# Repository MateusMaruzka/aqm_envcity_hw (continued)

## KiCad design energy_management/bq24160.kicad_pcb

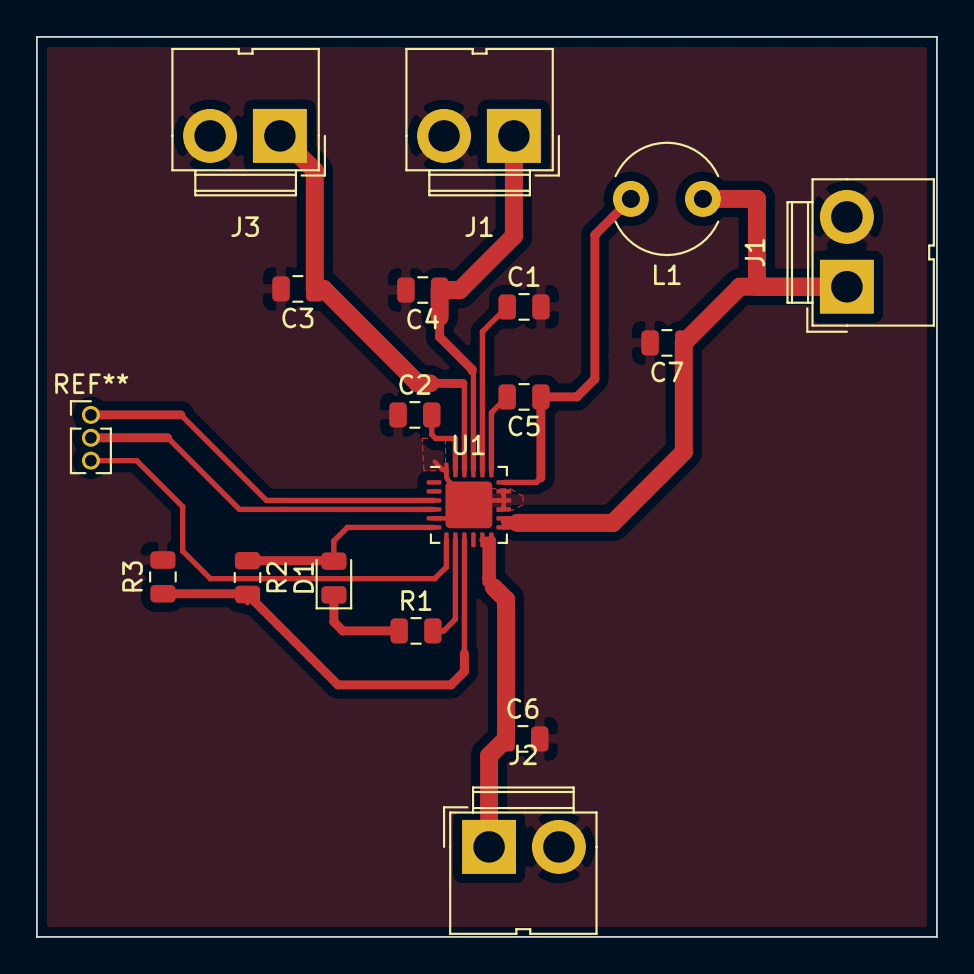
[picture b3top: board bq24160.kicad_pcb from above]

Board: 2 copper layers, 50.0 x 50.0 mm, 17 parts (0 on the bottom side), 13 nets.

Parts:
C1, C2: 4,7uF; C_0805_2012Metric
C3, C4, C6, C7: 1uF; C_0805_2012Metric
C5: 0,01uF; C_0805_2012Metric
D1: LED; LED_0805_2012Metric
J1, J1#2, J2: Conn_01x02_Male; JWT_A3963_1x02_P3.96mm_Vertical
J3: Conn_01x02_Female; JWT_A3963_1x02_P3.96mm_Vertical
L1: 1,5uH; L_Radial_D6.0mm_P4.00mm
R1: 1K; R_0805_2012Metric
R2: 10k; R_0805_2012Metric
R3: 10K; R_0805_2012Metric
U1: BQ24160RGET; QFN-24-1EP_4x4mm_P0.5mm_EP2.6x2.6mm

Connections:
/BAT_NTC: R2.2, R3.1, U1.9
/BOOT: C5.2, U1.19
/PMIDU: C2.2, U1.23
/STAT: R1.2, U1.8
/SW: C5.1, L1.2, U1.18
/VBAT: C6.1, J2.1, U1.11, U1.12
/VDRV: D1.2, R2.1, U1.6
/Vext_dc: C4.1, J1#2.1, U1.21
/Vsistema: C7.1, J1.1, L1.1, U1.13, U1.14
/Vusb: C3.1, J3.1, U1.22
GND: C1.2, C2.1, C3.2, C4.2, C6.2, C7.2, J1.2, J1#2.2, J2.2, J3.2, R3.2, U1.5, U1.15, U1.16, U1.17, U1.24, U1.25
unnamed: C1.1, U1.20
unnamed: D1.1, R1.1

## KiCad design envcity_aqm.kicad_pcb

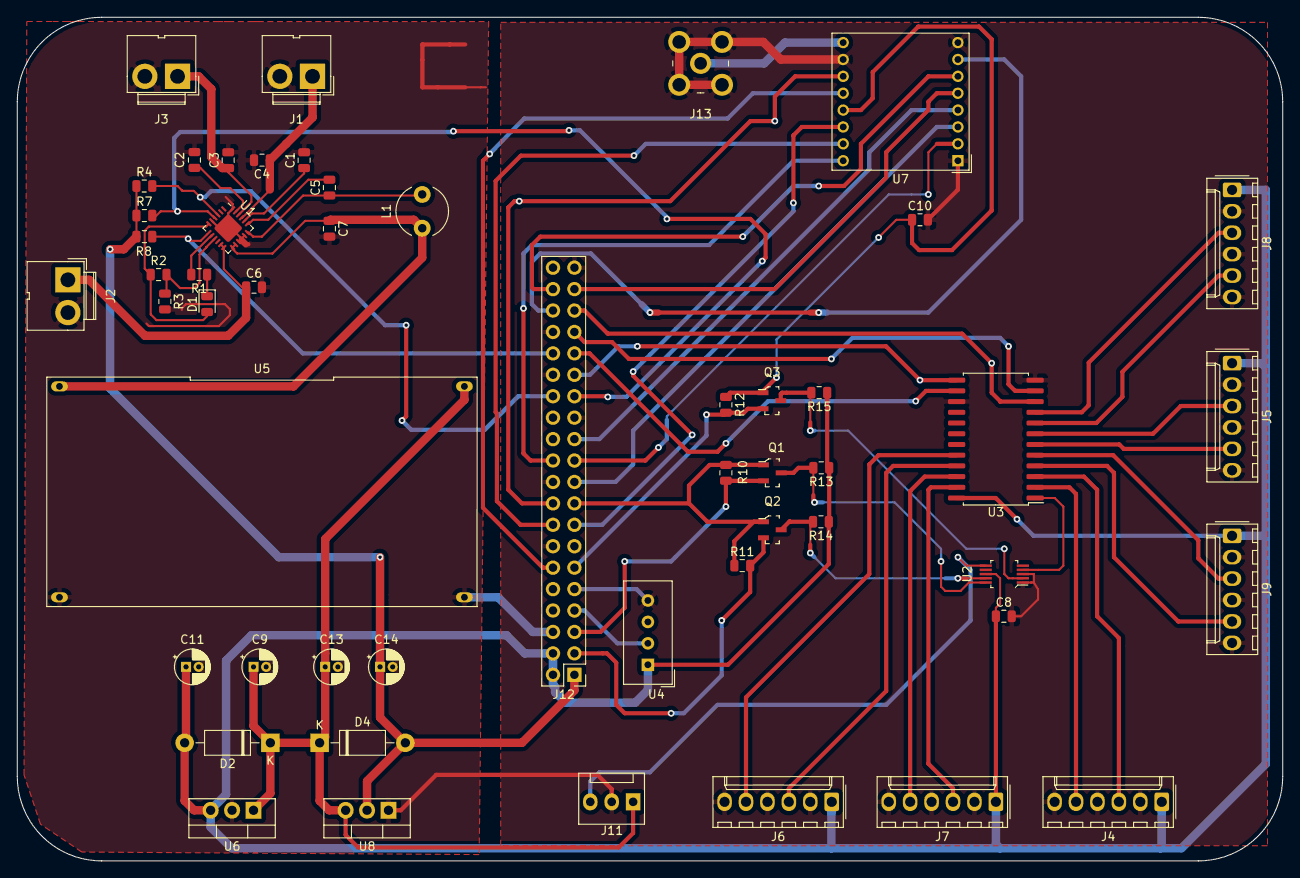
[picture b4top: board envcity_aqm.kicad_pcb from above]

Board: 2 copper layers, 150.0 x 100.0 mm, 52 parts (0 on the bottom side), 56 nets.

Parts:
C1, C2: 4,7uF; C_0805_2012Metric
C3, C4, C6, C7, C8: 1uF; C_0805_2012Metric
C5: 0,01uF; C_0805_2012Metric
C9, C13: 0,33uF; CP_Radial_D4.0mm_P1.50mm
C10: 100nF; C_0805_2012Metric
C11, C14: 0,1uF; CP_Radial_D4.0mm_P1.50mm
D1: LED; LED_0805_2012Metric
D2, D4: 1N4001; D_DO-41_SOD81_P10.16mm_Horizontal
J1, J2: Conn_01x02_Male; JWT_A3963_1x02_P3.96mm_Vertical
J3: Conn_01x02_Female; JWT_A3963_1x02_P3.96mm_Vertical
J4, J5, J6, J7, J8, J9: Conn_01x06_Male; Molex_KK-254_AE-6410-06A_1x06_P2.54mm_Vertical
J11: Conn_01x03_Female; FanPinHeader_1x03_P2.54mm_Vertical
J12: Conn_02x20_Odd_Even; PinHeader_2x20_P2.54mm_Vertical
J13: 5-1814400-1; RF_SMA_RightAngle_5-1814400-1
L1: 1,5uH; L_Radial_D6.0mm_P4.00mm
Q1, Q2, Q3: BSS138; SOT-23-3
R1: 1K; R_0805_2012Metric
R2, R4, R7, R8, R10, R11, R12, R13, R14, R15: 10k; R_0805_2012Metric
R3: 10K; R_0805_2012Metric
U1: BQ24160RGET; VQFN-24-1EP_4x4mm_P0.5mm_EP2.45x2.45mm
U2: ADS1115IDGST; MSOP-10_W3mm
U3: CD74HC4067M; SOIC-24W_7.5x15.4mm_P1.27mm
U4: DHT11; Aosong_DHT11_5.5x12.0_P2.54mm
U5: BUCK_BOOST_BOARD; DIP-4_1889_ELL
U6: LM7805_TO220; TO-220-3_Vertical
U7: RFM95W-915S2; HOPERF_RFM9XW_THT
U8: LM1117-3.3; TO-220-3_Vertical

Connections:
+3V3: C10.1, C14.1, D4.2, J12.1, J12.17, Q1.1, Q2.1, Q3.1, R4.1, R7.1, R8.1, R10.1, R11.1, R12.1, U7.13, U8.2
+5V: C8.1, C11.1, D2.2, J4.1, J5.1, J6.1, J7.1, J8.1, J9.1, J12.2, J12.4, R13.1, R14.1, R15.1, U2.8, U3.24, U4.1, U6.3
/9Vin: C9.1, C13.1, D2.1, D4.1, J11.1, U5.3, U6.1, U8.3
/ADS1115+MUX/AIN0: U2.4, U3.1
/AD_ALERT: Q3.3, R15.2, U2.2
/AD_SCL: Q1.3, R13.2, U2.10
/AD_SDA: Q2.3, R14.2, U2.9
/BQ_INT: J12.32, R8.2, U1.7
/BQ_SCL: J12.28, R4.2, U1.3
/BQ_SDA: J12.27, R7.2, U1.4
/DHT22: J12.7, U4.2
/DIO0: J12.15, U7.14
/DIO1: J12.16, U7.15
/DIO2: J12.22, U7.16
/DIO3: J12.18, U7.11
/DIO4: J12.12, U7.12
/DIO5: J12.36, U7.7
/Gerenciamento de Bateria/BAT_NTC: R2.2, R3.1, U1.9
/Gerenciamento de Bateria/BOOT: C5.2, U1.19
/Gerenciamento de Bateria/PMIDU: C2.2, U1.23
/Gerenciamento de Bateria/STAT: R1.2, U1.8
/Gerenciamento de Bateria/SW: C5.1, L1.2, U1.18
/Gerenciamento de Bateria/VBAT: C6.1, J2.1, U1.11, U1.12
/Gerenciamento de Bateria/VDRV: D1.2, R2.1, U1.6
/Gerenciamento de Bateria/Vext_dc: C4.1, J1.1, U1.21
/Gerenciamento de Bateria/Vusb: C3.1, J3.1, U1.22
/I0: J8.3, U3.9
/I1: J8.5, U3.8
/I2: J5.3, U3.7
/I3: J5.5, U3.6
/I4: J9.3, U3.5
/I5: J9.5, U3.4
/I6: J4.3, U3.3
/I7: J4.5, U3.2
/I8: J7.3, U3.23
/I9: J7.5, U3.22
/I10: J6.3, U3.21
/I11: J6.5, U3.20
/NSS: J12.37, U7.5
/RASP_INT0: J12.11, Q3.2, R12.2
/RASP_SCL0: J12.5, Q1.2, R10.2
/RASP_SDA0: J12.3, Q2.2, R11.2
/RESET: J12.38, U7.6
/Radio LoRa RFM95W/ANT: J13.2, U7.9
/Reguladores/Vin: C7.1, L1.1, U1.13, U1.14, U5.1
/S0: J12.35, U3.10
/S1: J12.33, U3.11
/S2: J12.31, U3.14
/S3: J12.29, U3.13
/SPI0_0: J12.19, U7.3
/SPI0_1: J12.21, U7.2
/SPI0_2: J12.23, U7.4
AIN2: J11.3, U2.6
GND: C1.2, C2.1, C3.2, C4.2, C6.2, C7.2, C8.2, C9.2, C10.2, C11.2, C13.2, C14.2, J1.2, J2.2, J3.2, J4.2, J4.4, J4.6, J5.2, J5.4, J5.6, J6.2, J6.4, J6.6, J7.2, J7.4, J7.6, J8.2, J8.4, J8.6, J9.2, J9.4, J9.6, J11.2, J12.6, J12.9, J12.14, J12.20, J12.25, J12.30, J12.34, J12.39, J13.1, R3.2, U1.5, U1.15, U1.16, U1.17, U1.24, U1.25, U2.1, U2.3, U3.12, U3.15, U4.4, U5.2, U5.4, U6.2, U7.1, U7.8, U7.10, U8.1
unnamed: C1.1, U1.20
unnamed: D1.1, R1.1

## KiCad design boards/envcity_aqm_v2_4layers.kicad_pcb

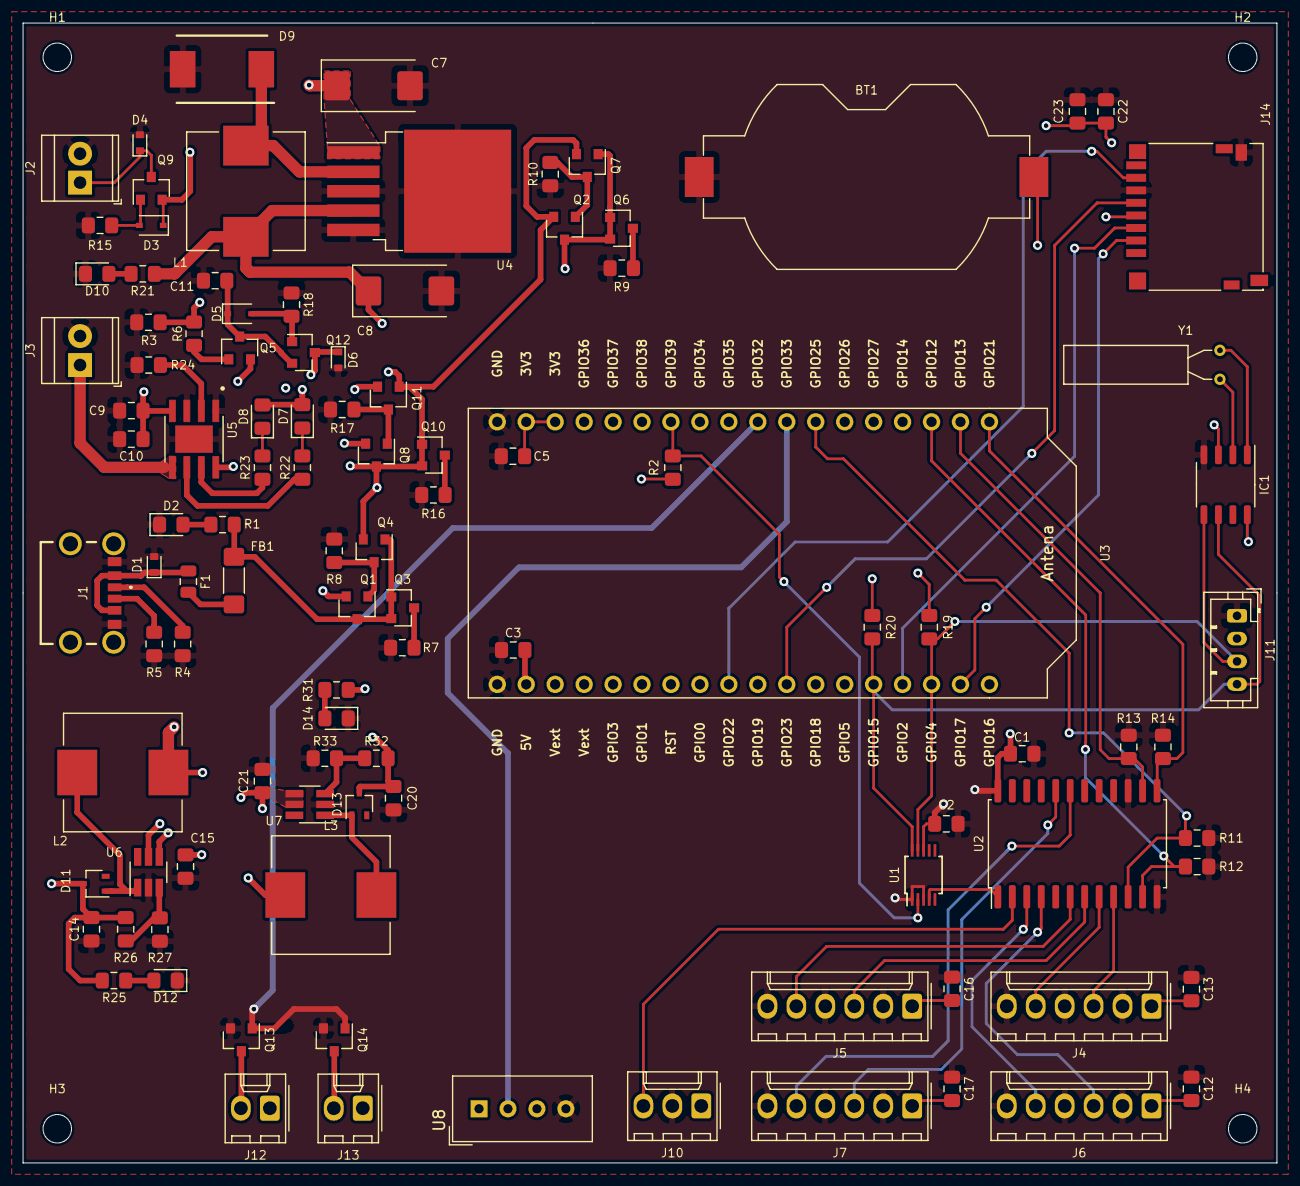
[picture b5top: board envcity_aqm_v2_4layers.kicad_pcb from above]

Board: 4 copper layers, 110.0 x 100.0 mm, 109 parts (0 on the bottom side), 67 nets.

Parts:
BT1: Battery_Cell; BatteryHolder_Keystone_1058_1x2032
C1, C9, C11, C22: 10uF; C_0805_2012Metric_Pad1.15x1.40mm_HandSolder
C2, C3, C5, C10, C12, C13, C16, C17, C23: 100nF; C_0805_2012Metric_Pad1.15x1.40mm_HandSolder
C7: 680uF - Tant; CP_EIA-7343-15_Kemet-W_Pad2.25x2.55mm_HandSolder
C8: 220uF-Tantalum; CP_EIA-7343-15_Kemet-W_Pad2.25x2.55mm_HandSolder
C14, C15, C20, C21: 22uF-X5R; C_0805_2012Metric_Pad1.15x1.40mm_HandSolder
D1, D4, D6: D_TVS_ALT; D_SOD-523
D2, D7, D8, D10, D12, D14: LED; LED_0805_2012Metric_Pad1.15x1.40mm_HandSolder
D3, D5: 5V; D_SOD-323
D9: SS34; DIOM8059X256N
D11, D13: BAT54W; SOT-323_SC-70
F1: Fuse; Fuse_0805_2012Metric
FB1: Ferrite_Bead; L_1806_4516Metric_Pad1.57x1.80mm_HandSolder
H1, H2, H3, H4: MountingHole; MountingHole_2.5mm
IC1: DS1307ZN+; SOP-8_3.9x4.9mm_P1.27mm
J1: 217175-0001; 2171750001
J2, J3: Screw_Terminal_01x02; TerminalBlock_TE_282834-2_1x02_P2.54mm_Horizontal
J4, J5, J6, J7: Conn_01x06_Male; Molex_KK-254_AE-6410-06A_1x06_P2.54mm_Vertical
J10: Conn_01x03_Male; Molex_KK-254_AE-6410-03A_1x03_P2.54mm_Vertical
J11: Conn_01x04_Male; JST_PH_B4B-PH-K_1x04_P2.00mm_Vertical
J12, J13: Conn_01x02_Male; Molex_KK-254_AE-6410-02A_1x02_P2.54mm_Vertical
J14: Micro_SD_Card; microSD_HC_Hirose_DM3D-SF
L1: 33uH; L_Wuerth_HCI-1040
L2, L3: 4.7 to 22uH; L_Wuerth_HCI-1040
Q1, Q2, Q8: DMG2301L; SOT-23
Q3, Q4, Q6, Q7, Q10, Q11: BC808; SOT-23
Q5, Q9, Q12: DMG2301L / DMP2045U; SOT-23
Q13, Q14: DMN10H220L; SOT-23
R1, R2, R11, R12, R13, R14, R19, R20, R21, R22, R23, R31: 4K7; R_0805_2012Metric_Pad1.15x1.40mm_HandSolder
R3, R6, R7, R9, R16: 10K; R_0805_2012Metric_Pad1.15x1.40mm_HandSolder
R4, R5: 5K1; R_0805_2012Metric_Pad1.15x1.40mm_HandSolder
R8, R10, R17: 47K; R_0805_2012Metric_Pad1.15x1.40mm_HandSolder
R15, R18, R33: 1K; R_0805_2012Metric_Pad1.15x1.40mm_HandSolder
R24: 2K; R_0805_2012Metric_Pad1.15x1.40mm_HandSolder
R25: 9K1; R_0805_2012Metric_Pad1.15x1.40mm_HandSolder
R26: 30K; R_0805_2012Metric_Pad1.15x1.40mm_HandSolder
R27: 2.2K; R_0805_2012Metric_Pad1.15x1.40mm_HandSolder
R32: 7K5; R_0805_2012Metric_Pad1.15x1.40mm_HandSolder
U1: ADS1115IDGS; TSSOP-10_3x3mm_P0.5mm
U2: CD74HC4067M; SOIC-24W_7.5x15.4mm_P1.27mm
U3: Heltec_Wifi_LoRa_V2; Heltec_WiFi_LoRa_V2
U4: LM2596S-5; TO-263-5_TabPin3
U5: TP4056; SOP127P600X175-9N
U6, U7: MT3608; SOT-23-6_Handsoldering
U8: DHT11; Aosong_DHT11_5.5x12.0_P2.54mm
Y1: 32,768KHz; Crystal_AT310_D3.0mm_L10.0mm_Horizontal

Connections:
+3V3: C5.1, C22.1, C23.1, J14.4, R2.1, R19.1, R20.1, U3.34, U3.35
+5V: C1.1, C2.1, C3.1, C9.1, C10.1, C12.1, C13.1, C16.1, C17.1, C20.1, D7.2, D8.2, D13.3, IC1.8, J4.1, J5.1, J6.1, J7.1, J11.2, J12.1, J13.1, R31.1, R32.1, U1.8, U2.24, U3.2, U5.4, U8.1
+9V: C14.1, D11.3, J10.1, R25.1, R26.1
/ADS_ALERT: R2.2, U1.2, U3.30
/ADS_SCL: IC1.6, J11.4, R20.2, U1.10, U3.14
/ADS_SDA: IC1.5, J11.3, R19.2, U1.9, U3.16
/AIN0: U1.4, U2.1
/BST_FB_5V: R32.2, R33.1, U7.3
/BST_FB_9V: R26.2, R27.1, U6.3
/BST_SW_5V: D13.1, L3.2, U7.1
/BST_SW_9V: D11.1, L2.2, U6.1
/CC1: J1.A5, R4.1
/CC2: J1.B5, R5.1
/DHT11: U3.26, U8.2
/FAN1: Q13.1, Q14.1, U3.27
/I0: J4.3, U2.9
/I1: J4.5, U2.8
/I2: J5.3, U2.7
/I3: J5.5, U2.6
/I5: J6.3, U2.4
/I6: J6.5, U2.3
/I7: J10.3, U2.2
/I11: J7.3, U2.20
/I12: J7.5, U2.19
/S0: R11.1, U2.10, U3.25
/S1: R12.1, U2.11, U3.21
/S2: R13.1, U2.14, U3.20
/S3: R14.1, U2.13, U3.19
/SD_CLK: J14.5, U3.11
/SD_CS: J14.2, U3.17
/SD_MISO: J14.7, U3.9
/SD_MOSI: J14.3, U3.15
GND: BT1.2, C1.2, C2.2, C3.2, C5.2, C7.2, C8.2, C9.2, C10.2, C11.2, C12.2, C13.2, C14.2, C15.2, C16.2, C17.2, C20.2, C21.2, C22.2, C23.2, D1.2, D2.1, D4.2, D6.2, D9.2, D10.1, D12.1, D14.1, IC1.4, J1.A12, J1.B12, J2.2, J3.2, J4.2, J4.4, J4.6, J5.2, J5.4, J5.6, J6.2, J6.4, J6.6, J7.2, J7.4, J7.6, J10.2, J11.1, J14.6, J14.9, Q13.2, Q14.2, R3.1, R4.2, R5.2, R7.2, R8.2, R9.2, R10.2, R11.2, R12.2, R13.2, R14.2, R15.2, R16.2, R17.2, R18.2, R24.2, R27.2, R33.2, U1.1, U1.3, U2.12, U2.15, U3.1, U3.36, U4.3, U4.5, U5.1, U5.3, U5.9, U6.2, U7.2, U8.4
unnamed: BT1.1, IC1.3
unnamed: D2.2, R1.2
unnamed: D3.2, Q9.1, R15.1
unnamed: D5.2, Q12.1, R18.1
unnamed: D7.1, R22.1
unnamed: D8.1, R23.1
unnamed: D9.1, L1.2, U4.2
unnamed: D10.2, R21.2
unnamed: D12.2, R25.2
unnamed: D14.2, R31.2
unnamed: F1.1, FB1.1
unnamed: IC1.1, Y1.1
unnamed: IC1.2, Y1.2
unnamed: J12.2, Q13.3
unnamed: J13.2, Q14.3
unnamed: Q1.1, Q4.3, R8.1
unnamed: Q2.1, Q7.3, R10.1
unnamed: Q3.3, R7.1
unnamed: Q5.1, R6.2
unnamed: Q6.3, R9.1
unnamed: Q10.3, R16.1
unnamed: Q8.1, Q11.3, R17.1
unnamed: R22.2, U5.6
unnamed: R23.2, U5.7
unnamed: R24.1, U5.2
Vbat: D6.1, J3.1, Q12.3, U5.5
Vbat_protected: C11.1, D5.1, Q5.3, Q12.2
Vexternal: Q1.2, Q2.2, Q4.2, Q7.2, Q8.3, Q10.1, Q10.2, Q11.1, R3.2, R6.1, U5.8
Vsolar: D4.1, J2.1, Q9.3
Vsolar_protected: C7.1, D3.1, Q9.2, U4.1
Vsolar_reg: C8.1, L1.1, Q2.3, Q6.1, Q6.2, Q7.1, R21.1, U4.4
Vsys: C15.1, C21.1, L2.1, L3.1, Q5.2, Q8.2, Q11.2, U6.4, U6.5, U7.4, U7.5
Vusb: D1.1, F1.2, J1.A9, J1.B9
Vusb_protected: FB1.2, Q1.3, Q3.1, Q3.2, Q4.1, R1.1

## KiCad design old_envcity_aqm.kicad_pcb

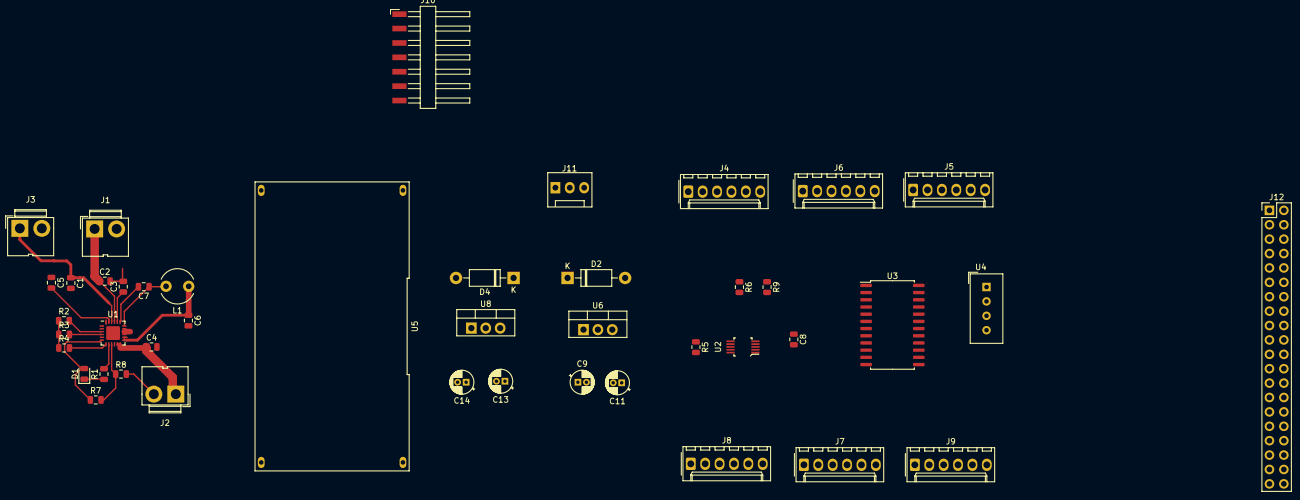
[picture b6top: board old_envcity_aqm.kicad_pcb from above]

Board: 2 copper layers, 44 parts (0 on the bottom side), 21 nets.

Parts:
C1, C2, C4, C6, C8: 1uF; C_0805_2012Metric
C3, C5: 4,7uF; C_0805_2012Metric
C7: 0,01uF; C_0805_2012Metric
C9, C13: 0,33uF; CP_Radial_D4.0mm_P1.50mm
C11, C14: 0,1uF; CP_Radial_D4.0mm_P1.50mm
D1: LED; LED_0805_2012Metric
D2, D4: 1N4001; D_DO-41_SOD81_P10.16mm_Horizontal
J1, J2: Conn_01x02_Male; JWT_A3963_1x02_P3.96mm_Vertical
J3: Conn_01x02_Female; JWT_A3963_1x02_P3.96mm_Vertical
J4, J5, J6, J7, J8, J9: Conn_01x06_Male; Molex_KK-254_AE-6410-06A_1x06_P2.54mm_Vertical
J10: Conn_01x07_Female; Harwin_M20-89007xx_1x07_P2.54mm_Horizontal
J11: Conn_01x03_Female; FanPinHeader_1x03_P2.54mm_Vertical
J12: Conn_02x20_Odd_Even; PinHeader_2x20_P2.54mm_Vertical
L1: 1,5uH; L_Radial_D6.0mm_P4.00mm
R1, R2, R3, R4: 1K; R_0805_2012Metric
R5, R6, R9: 4,7k; R_0805_2012Metric
R7: 10k; R_0805_2012Metric
R8: 10K; R_0805_2012Metric
U1: BQ24160RGET; VQFN-24-1EP_4x4mm_P0.5mm_EP2.45x2.45mm
U2: ADS1115IDGST; MSOP-10_W3mm
U3: CD74HC4067M; SOIC-24W_7.5x15.4mm_P1.27mm
U4: DHT11; Aosong_DHT11_5.5x12.0_P2.54mm
U5: BUCK_BOOST_BOARD; DIP-4_1889_ELL
U6: LM7805_TO220; TO-220-3_Vertical
U8: LM1117-3.3; TO-220-3_Vertical

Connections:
+3V3: C14.1, D4.2, R2.1, R3.1, R4.1, U8.2
+5V: C8.1, C11.1, D2.2, J4.1, J5.1, J6.1, J7.1, J8.1, J9.1, J12.2, J12.4, R5.1, R6.1, R9.1, U2.8, U3.24, U4.1, U6.3
/ADS1115+MUX/AIN0: U2.4, U3.1
/BAT_NTC: R7.2, R8.1, U1.9
/BOOT: C7.2, U1.19
/Reguladores/9V_BUCK-BOOST: C9.1, C13.1, D2.1, D4.1, U6.1, U8.3
/STAT: R1.2, U1.8
/SW: C7.1, L1.2, U1.18
/Sensores/DHT_OUT: J12.13, U4.2
/VBAT: C4.1, J2.1, U1.11, U1.12
/VDRV: D1.2, R7.1, U1.6
/Vext_dc: C2.1, J1.1, U1.21
/Vusb: C1.1, J3.1, U1.22
AD_ALERT: R9.2, U2.2
AD_SCL: R5.2, U2.10
AD_SDA: R6.2, U2.9
GND: C1.2, C2.2, C3.2, C4.2, C5.1, C6.2, C8.2, C9.2, C11.2, C13.2, C14.2, J1.2, J2.2, J3.2, J4.2, J4.4, J4.6, J5.2, J5.4, J5.6, J6.2, J6.4, J6.6, J7.2, J7.4, J7.6, J8.2, J8.4, J8.6, J9.2, J9.4, J9.6, J11.2, R8.2, U1.5, U1.15, U1.16, U1.17, U1.24, U2.1, U2.3, U3.12, U3.15, U4.4, U5.2, U5.4, U6.2, U8.1
unnamed: C3.1, U1.20
unnamed: C5.2, U1.23
unnamed: D1.1, R1.1
Vsistema: C6.1, L1.1, U1.13, U1.14

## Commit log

2022-01-04 Arquivos do projeto
2022-01-06 Adicionando radio LoRa. Criando um .sch para a Raspberry e para o radio
2022-01-08 Versão v0 finalizada. Adiciona pasta para os arquivos de saída e de fabricacao.
2022-01-13 Projeto da estação de monitoramento da qualidade do ar dividido em subprojetos. Cada subprojeto é um projeto independente do kicad.
2022-01-16 Conexão entre os componentes. Correção da lib do buck-boost. Separação do 3v3 da raspberry e do 3v3 do regulador
2022-01-17 Adicionando circuito para proteção de Vext_dc e Vusb; A explicação do circuito esta no esquematico
2022-01-17 Add proteção contra reversao de polaridade no conector da bateria
2022-01-17 Add pdf do esquemático. Add arquivo do kicad p/ a PCB.
2022-01-20 Roteamento da PCB pronto; Agora o 3v3 da raspberry alimenta os resistores de pull up da comunicacao i2c do bq24160
2022-01-25 Roteamento completo. Aprovado pelo professor Claudinei.
2022-01-28 Add mounting holes. Corrige footprint dos conectores da bateria e alimentacao
2022-02-07 Add tear drops
2022-06-02 vish
2023-01-31 new aqm board version
2023-01-31 add gitignore
2023-02-01 Add placa com 4 camadas. Add dht11.
2023-04-28 Changing USB conn and add esp32-c3-mini-wroom
2023-04-28 add rfm95
2023-04-29 Add conversor 3v3. Add rfm. Changing esp32c3-mini to esp32-s2
2023-04-29 separa a alimentacao do esp32 e do rfm. add 2 conectores para alphasense. Add conector pms5003
2023-05-02 Add um monte de coisa
2023-05-03 Add diversas trilhas e corrige 3dmodel
2023-05-03 circuito esp32 ok
2023-05-05 Alterando os indutores. Add diversos 3dmodel. Alterando cristal rtc. Refaz algumas trilhas
2023-05-06 Roteamento do cartao sd (incompleto). Roteamento USB com controle de impedancia ok.
2023-05-07 add simulacao circ boost e zvd
2023-05-09 Terminando o posicionamento dos components
2023-05-10 mudando posicoes
2023-05-12 add 3dmodel cr2032 e algumas trilhas
2023-05-17 Alteracoes no roteamento
2023-05-19 add 3d model pms. add mais trilhas
2023-05-19 add trilhas
2023-05-24 Trocando o modelo do cartaoSD
2023-05-26 running DRC and fixing some errors
2023-05-29 Corrigindo LCSC part #
2023-06-10 board ok. Add tps54202
2023-06-13 add novo conversor
2023-06-13 add gerber. corrige pcb
2023-08-16 remove tranqueiras
2023-08-17 altera componentes
2023-08-26 Add logo na pcb
    Add a logo
2023-08-28 add novo esp32
2025-03-08 add sim
2025-03-08 add flyback diode. add pulldown on fan switch fet
2025-03-08 change simulations path
